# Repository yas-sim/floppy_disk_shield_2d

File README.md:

# Floppy Disk Shield for Arduino UNO

## Caveat and Disclaimer - Read before you build a fd-shield  

- I don't own any responsibility for the data loss or physical damage on your floppy disks or computer assets caused by the use of hardware and software included in this project.
- Hardware compatibility (especially, FDD and FD-Shield compatibility) is not guaranteed. Your FDD may now work with the FD-Shield.  
- The magnetic flux power on the old floppy disks are dropping and getting weak as time passes. Read-out data integrity with this system is not guaranteed.
- Recommended to use newer FDD. The old FDD may have problems on the magnetic head such as contamination, worn out or mechanical misalignment.

## Announcement  
23-Sep 2022 : Preview release - Feature to write back the floppy images to FD is supported. Use `duplicate.py` to write the `*.raw` floppy image data to a floopy disk. Arduino firmware update and closing `JP5` on the fd-capture shield are required to enable the feature.   
23-Sep 2022 : Preview release - イメージの書き戻しもできるようになりました。Arduinoファームウエアの更新と`JP5`ジャンパーのショートをすると書き込みができるようになります。   

## Description
This is a project to develop a system for preserving old 2D/2DD floppy disk data.  
The system can preserve entire floppy disk data regardless whether it's normal or not. That means the system can read and preserve copy protect information in the bit-stream file as it is.  
The recorded bit-stream file can be decoded and restore the contents anytime later.  
The system includes a bit-stream data to D77/D88 emulator disk image converter. You can read the floppy disk with this tool and generate the disk images.  
これは古い2D/2DDフロッピーディスクのデータを保存するためのシステムを作るプロジェクトです。  
このシステムを使うことで仕様にのっとった正しい信号も非正規の信号も全てそのまま保存することが可能です。つまり、このシステムではコピープロテクトのための情報まで含めてビットストリームデータとして保存することが可能です。  
記録されたビットストリームデータは後でデコード、解読を行うことで情報を取り出すことが可能です。  
このシステムにはビットストリームデータからエミュレータ互換のイメージファイル(D77/D88)を生成するためのコンバーターも含んでいます。実際のフロッピーを読み取り、ディスクイメージを生成することが可能です。  

The system consists of the hardware and software:  
システムはハードウエアとソフトウエアから構成されます:

**Hardware**  
|Item|Description|
|:----|:----|
|Arduino UNO|Arduino UNO. The firmware uses ATMega328 specific regiter. The other Arduino board may not work|
|Floppy disk shield for Arduino|Design data is included. Both schematics and PCB data are available (`./kicad/*`)<br>Rev.A design has bugs. Rev.B and beyond are basically comatible and has same function.<br>KiCAD用のPCBの設計データも提供されています(./kicad/*)<br>Rev.A and Rev.Fにはバグがあります。Rev.B以降は基本的に同じ機能です|
|Floppy disk drive|2D/2DD/2HD FDD. 3.5" or 5.25" FDD (+ power supply and ribbon cable). 300rpm drive is recommended but 360rpm 2HD drive will work as a 2DD drive. The FD-shield can detect the track density (2D or 2DD/2HD, 80 tracks or 160 tracks) and spindle spin speed (300rpm or 360rpm)|  

**Software**  

|Name|Description|
|:--------|:-----------|
|[`fdcapture.ino`](./docs/fdcapture_ino.md)|Arduino firmware (sketch) for the floppy shield<br> (`./fdcapture/fdcapture.ino`)|
|[`capture.py`](./docs/capture.md)|Floppy image capture tool (FD->image).<br>Transfers raw bitstream data from Arduino to a PC (foremerly, `transfer.py`)|
|[`duplicate.py`](./docs/duplicate.md)|Floppy image write back tool (image->FD).<br>Transfers raw bitstream data from a PC to Arduino. Close '`JP5`' jumper pad on the FD capture shield to enable the write feature.|
|[`bs2d77.py`](./docs/bs2d77.md)|Bit-stream data (.raw) to emulator disk image (D77/D88) converter.<br> The program generates modified D77 image data (D77mod). D77mod specification is [here](docs/D77mod_format.md). The D77mod uses some reserved bytes in the header but it is designed to keep backward compatibility with the standard D77 disk images. The D77mod image should work with emulators which supports regular D77/D88 disk images.|
|[`bs2hfe`](./docs/bs2hfe.md)|Bit-stream data (.raw) to .HFE floppy image format.<br>The .hfe disk image format is used for the [HxC FDD emulator device](https://hxc2001.com/download/floppy_drive_emulator/).|
|[`bs_inspect.py`](./docs/bs_inspect.md)|Data inspection/analyze tool for bit-stream data|
|[`d77_inspect.py`](./docs/d77_inspect.md)|Data inspection/analyze tool for D77/D88 disk image data|
|`floppylib.py`|A library which provides fundamental floppy disk functions.<br> This library is including data-separator, digital VFO, MFM decoder and IBM format parser|
|`d77dec.py`|Convert a D77/D88 disk image data to a JSON (plane text) file|
|`d77enc.py`|Generate a D77/D88 disk image data from a JSON file|
|`d77lib.py`|A libray which provides basic D77/D88 floppy disk image manipulation functions|
|[`kfx2bs.py`](./docs/kfx2bs.md)|[**KyroFlux**](https://www.kryoflux.com/) raw-bitstream data to fd-shield bit-stream data converter. You can capture FD image with KryoFlux and use it.|

### Updates  
|Date|Description|
|-|-|
|Sep 2022|Updated PCB design. Changed the 'Write Gate' jumper from jumper pad to jumper pin header for easy setting.|
|Sep 2022|Added support for the image write back feature (image->fd). Arduino firmware update and closing `JP5` on the fd-capture shield are required to enable the feature.|
|Sep 2022|Added RAW to HFE file converter (bs2hfe.py)|
|Aug 2022|Backported data-separator and VFO algorithm from [fdc_bitstream](https://github.com/yas-sim/fdc_bitstream) project. The latest VFO algorithm improved the accuracy of the data reading / decoding.|

## fdc_bitstream  
The [`fdc_bitstream`](https://github.com/yas-sim/fdc_bitstream) is my project that provides a bit-accurate C++ software FDC library. The fdc_bitstream project includes a disk image converter and image analyzer. Those software are written in C++, so they are faster than the converters in this project. Also, they are developed recently and have better algorithms for format conversion.  Please try `image_converter` in the `fdc_bitstream` project as well.  
[`fdc_bitstream`](https://github.com/yas-sim/fdc_bitstream)はビット精度で正確なソフトウエアFDCを開発するプロジェクトです。fdc_bitstreamプロジェクトにもイメージ変換ツールとイメージ解析ツールが含まれています。これらのツールはC++でかかれており、より高速です。またこちらのほうが開発が後なのでより良いアルゴリズムが使われており、イメージ変換の正確性も上がっています。fdc_bitstreamプロジェクトのimage_converterもお試しください。  

### System Diagram

## FD-Shield - How It Works

---------

## Introduction of Features in the Support Tools

* `bs_inspect.py`  
This tool provides featurs to analyze or check the bitstream data and its quality.  
	* Visualize track data including address mark and sector data occupancies.
	* Visualize data timing history.
	* Visualize data timing histogram.
	* Read all IDs in the tracks.
	* Read all sectors in the tracks.
	* MFM data dump.
	* ASCII data dump (display pritable/readable data).
	* Tweak parameters (VFO high/low gain value, sampling frequency, FDD spin speed) .

### Track visualizer  
You can check the address marks and sector body overlap status with this feature. The entire track data is shown in the window. The yellow vertical line indicates the position of the index hole (it appears when you capture the track data with --read_overlap option). This feature can show the decoded MFM data at the point of the mouse cursor.   

* Legend:  
	* Red ID               : ID CRC Error
	* Green virtical line  : ID AM / Index AM
	* Cyan virtical line   : DAM / DDAM
	* Cyan horizontal line : Sector data (normal)
	* Magenta horizontal line : Sector data (Data CRC error)
	* Red cross mark       : Record not found error
	* Yellow virtical line : Index hole  
<br>  

* Example of a normal track  

* Example of a protected track  

### Bitstream visualizer  
You can check how VFO follows the variation of pulse pitch with the bitstream visualizer.  
The VFO tries to keep the data pulse be the center of the bit cell as much as possible by tweaking the oscillation frequency (= the bit cell width).  

### Bitstream timing histogram viewer
* Good case 
* Bad case - Usually, this may be caused by the spindle speed fluctuation (that causes data pulse pitch variation in a track), or data written by multiple drives (written with drives with different spindle motor speeds).  

### Pulse (bit) pitch visualizer  
You can check the pulse pitch fluctuation throughout a track with the pulse pitch visualizer. The stabler pitch, the easier MFM decode or data read.  
- Stable pitch  

- Unstable pitch. Heavily fluctuated. It's so hard to follow by the VFO. May fail data retrieving.  

---------

## How to use (Image capture) - 使い方

1. Build Floppy shield for Arduino UNO - シールド製作  
- PCB design files can be found in the `./kicad` directory
2. Burn the floppy disk shield firmware (sketch) to Arduino UNO - Arduio UNOにファームウエアを書き込む  
Use `fdcapture.ino`
3. Assemble the system - システムを接続
- Attach a floppy shield to an Arduino UNO
- Connect a floppy shield and a floppy disk drive with a 36pin ribon cable
- Connect Arduino UNO to PC via USB cable
4. Read raw bit-stream data from a floppy disk - フロッピーからビットストリームデータを生成  
- Insert a 2D floppy disk to the floppy disk drive (FDD)
- Run following command on the Windows PC:
```sh
python capture.py -o image_name.raw --read_overlap 5 [--media_type 2D|2DD]
```
- `capture.py` will search COM port for Arduino UNO and use it.  
- `--read_overlap` option specifies how much data to read on the 2nd lap in percent.  
- `--media_type` option specifies the media type to read. `2D` or `2DD` are available.  
Note: The `fdcapture.ino` can identify the drive type (2D or 2DD) but not the media type.    
5. Convert raw bit-stream data into emulator image data (D77mod) -- ビットストリームからディスクイメージファイルを生成
```sh
python bs2d77.py -i image_name.raw --abort_id
```
- `image_name.d77` will be generated.  
**Note:** The `--abort_id` option enables abort reading track image when the same sector ID is detected. The FD-shield can read the top of the 2nd lap with `--read_overlap` option. This overlapped track data may contain the same sector data twice. This option will prevent from generating the same sector in a track.  

## Image write back (cloning)  
1. Setup the system as the same as image captureing.  
	- The same `fdcapture.ino` firmware works for both `capture.py' and 'duplicate.y' but updating to the latest firmware is required. Use Arduino IDE to update the firmware (Arduino program).    
	- Close `JP5` jumper pad on the fd-capture shield.  
2. Run '`duplicate.py`' to write back a '`*.raw`' floppy image to a floppy disk.  
```sh
python duplicate.py -i disk_image.raw
```

## How to make your own FD-shield PCB (FD-shield PCBの作り方)  
- PCB design data and the data for PCB manufacturing (Garber data and drill data) are included in this project. You can order your PCB at a PCB manufacturing service company. I used 'Fusion PCB' from Seeed Studio. (cost would be around $35 for 10 PCBs incl. delivery fee)    
- PCB設計データとPCB製造データ(ガーバー、ドリル)はこのプロジェクトに含まれています。PCB製造サービス会社に製造を依頼してPCBを手に入れることができます。私はSeeed StudioのFusion PCBを利用しました。(10枚で4K円くらい？ 送料込み)   

|File|Description|  
|---|---|  
|pcb_mfg_data/fdshield-dip-rev-h.zip|PCB manufacturing data. DIP version. Rev.H (Write Gate pin header)|  
|kicad/fdshield-dip/fdshield/fdshield.kicad_pro|KiCad v6 design file (DIP)|  
|kicad/fdshield-sop/fdshield/fdshield.kicad_pro|KiCad v6 design file (SOP)|  

## Accessory Tools  
1. FDD spindle motor speed calibration tool  
This tool measures the index hole to index hole time and show it on the screen. You can tweak a variable register on the FDD control board to adjust the spindle speed.  
**CAUTION**: There might be multiple variable registers on the FDD control board. If you are unsure which one is the right one, do not turn it, or your FDD will become unfunctional.  
- How to use:  
	1. Set up `fdcapture` shield - Connect Arduino UNO, fdcapture shield, and FDD.   
	2. Insert a floppy disk into the FDD.  
	3. Run `spindle_calibration_tool.py`

## Current Development Status
**Done:**
- Read floppy disk images (2D disk on 2D drive, 2DD disk on 2D deive, 2D disk on 2DD/2HD drive)
- Write floppy disk image to floppy disk (2D images are tested)  
- Drive type auto datection (2D or 2DD/2HD)
- Drive spindle revolution measurement 
- Generates D77mod disk images from the raw bitstream data (RAW->D77)
- RAW->HFE file converter
- Bit stream file quality inspection tool (bs_inspect.py)

## Test Environment

- Windows 10 1909 / Windows 11 21H2
- Arduino UNO
- Floppy disk shield for Arduino
- FDDs (table below)

|P/N|Mfg|FF|Description|
|:----|:----|:----:|:----|
|YD-580 1354|YE-Data|5.25"|2D, 300rpm, for Fujitsu FM-7|
|MD5201|Canon|5.25"|2D, 300rpm|
|FD-55B-01-U 19307110-01|TEAC|5.25"|2D, 300rpm|
|FD55-GFR 19307673-93|TEAC|5.25"|2DD/2HD, 360rpm, for DOS/V|
|YD625-1525|YE-Data|3.5"|2D, 300rpm, for Fujitsu FM-77|
|FD-235HG 19307773-04|TEAC|3.5"|2DD/2HD, 300/360rpm, Fixed to DS1|
|OSD E26J|Citizen|3.5"|2DD/2HD, 300/360rpm, for PX9821Xa?|
|JU-256A236P|Panasonic|3.5"|2DD/2HD, 300/360rpm, for DOS/V|
|FD1231T 134-506790-011-0|NEC|3.5"|2DD/2HD, 300/360rpm, for PC9821|
|DF354H068C|ALPS|3.5"|2DD/2HD, 300/360rpm, for DOS/V|

---------------

## Addendum

### FD-shield - 3D view

### FD-shield - Schematics  
Y1 (Xtal) = 4MHz X'tal.  
U6 must be '74HC**U**04' (unbuffered type). The standard '74HC04' doesn't work.  
The other logic ICs can be either one of '74LS' or '74HC'.  

[PDF](resources/fdshield-schematics.pdf)

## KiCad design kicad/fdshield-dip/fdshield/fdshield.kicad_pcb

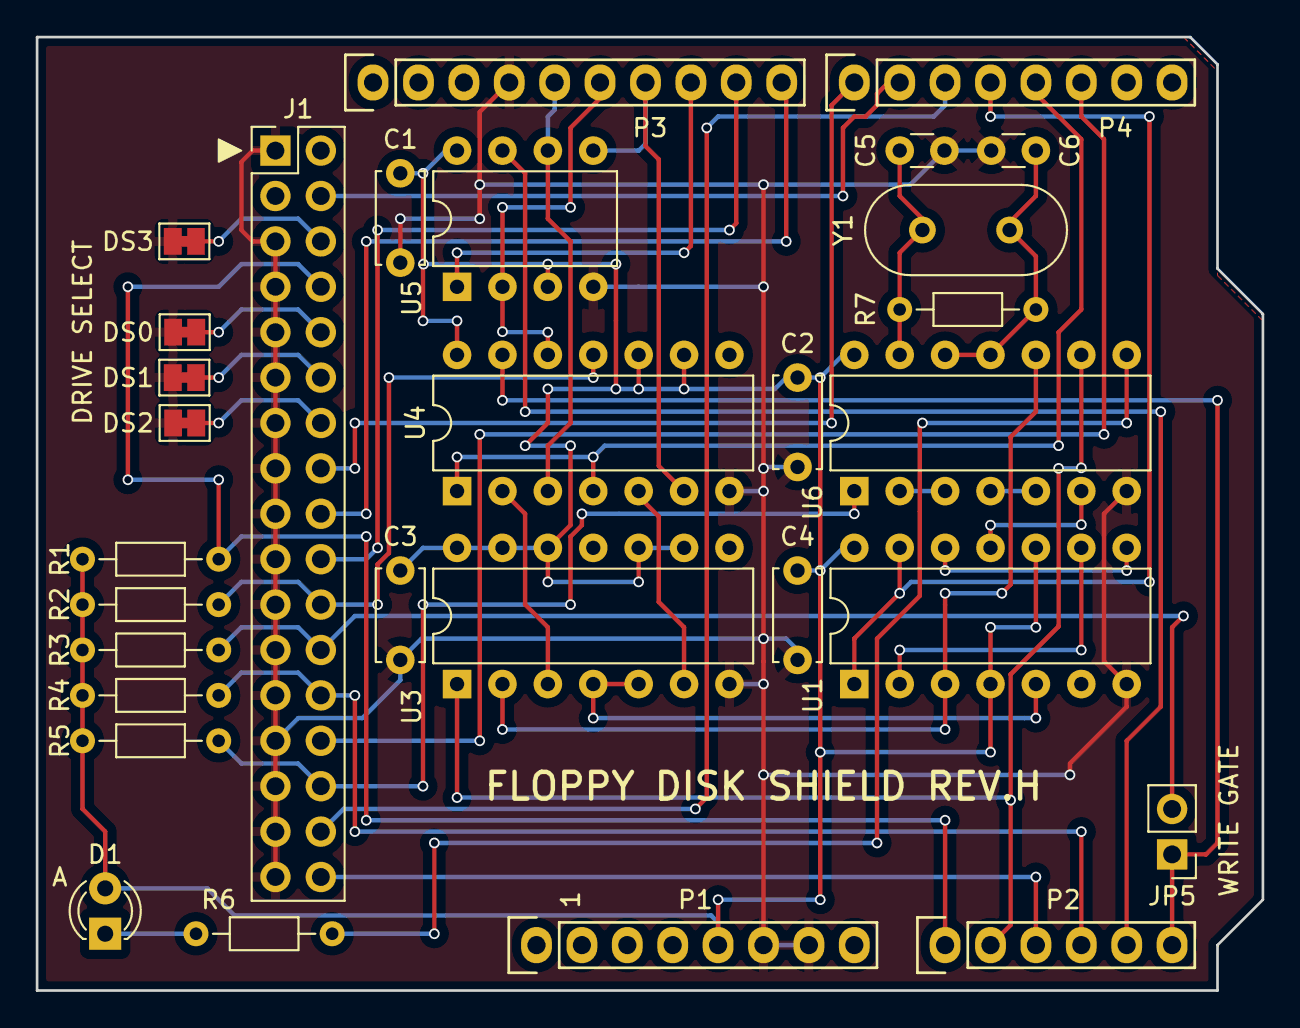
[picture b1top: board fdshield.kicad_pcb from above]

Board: 2 copper layers, 68.6 x 53.3 mm, 30 parts (0 on the bottom side), 40 nets.

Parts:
C1, C2, C3, C4: 0.1u; C_Disc_D5.0mm_W2.5mm_P5.00mm
C5, C6: 22p; C_Disc_D3.0mm_W1.6mm_P2.50mm
D1: LED; LED_D3.0mm
DS0, DS1, DS2, DS3: SolderJumper_2_Bridged; SolderJumper-2_P1.3mm_Bridged_Pad1.0x1.5mm
J1: Conn_02x17_Odd_Even; PinHeader_2x17_P2.54mm_Vertical
JP5: WRITE GATE; PinHeader_1x02_P2.54mm_Vertical
P1: Power; Socket_Strip_Arduino_1x08
P2: Analog; Socket_Strip_Arduino_1x06
P3: Digital; Socket_Strip_Arduino_1x10
P4: Digital; Socket_Strip_Arduino_1x08
R1, R2, R3, R4, R5: 150; R_Axial_DIN0204_L3.6mm_D1.6mm_P7.62mm_Horizontal
R6: 470; R_Axial_DIN0204_L3.6mm_D1.6mm_P7.62mm_Horizontal
R7: 1M; R_Axial_DIN0204_L3.6mm_D1.6mm_P7.62mm_Horizontal
U1: 74LS74; DIP-14_W7.62mm
U3: 74LS08; DIP-14_W7.62mm
U4: 74LS125; DIP-14_W7.62mm
U5: 23LCxxx; DIP-8_W7.62mm
U6: 74HCU04; DIP-14_W7.62mm
Y1: Crystal; Crystal_HC49-U_Vertical

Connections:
+5V: C1.1, C2.1, C3.1, C4.1, D1.2 (A), P1.5, R1.1, R2.1, R3.1, R4.1, R5.1, U1.4 (~S), U1.10 (~S), U1.14 (VCC), U3.9, U3.10, U3.12, U3.13, U3.14 (VCC), U4.9, U4.10, U4.14 (VCC), U5.3 (~WP), U5.8 (VCC), U6.14 (VCC)
/2: J1.28, P4.6
/3(**): P4.5, U4.1, U4.4
/4: P4.4, U1.1 (~R), U1.13 (~R)
/5(**): J1.32, P4.3
/6(**): J1.4, P4.2
/7: J1.16, P4.1
/8: J1.18, P3.10
/9(**): J1.20, P3.9
/10(**/SS): P3.8, U5.1 (~CS)
/11(**/MOSI): P3.7, U4.6, U5.5 (MOSI)
/12(MISO): P3.6, U4.12, U5.2 (MISO)
/13(SCK): P3.5, U4.3, U5.6 (SCK)
/A0: J1.8, P2.1, R1.2
/A1: P2.2, U3.1, U6.9
/A2: J1.34, P2.3
/A3: J1.26, P2.4, R4.2
/A4: P2.5, U5.7 (~HOLD)
/A5: JP5.1 (A), P2.6, U4.13
/CAP_CLK: U1.3 (C), U3.2, U6.10
/DS0: DS0.1 (A), J1.10
/DS1: DS1.1 (A), J1.12
/DS2: DS2.1 (A), J1.14
/DS3: DS3.1 (A), J1.6
/RD: J1.30, R5.2, U6.1
/WD: J1.22, R2.2, U4.11
/WG: J1.24, JP5.2 (B), R3.2
GND: C1.2, C2.2, C3.2, C4.2, C5.2, C6.2, DS0.2 (B), DS1.2 (B), DS2.2 (B), DS3.2 (B), J1.1, J1.5, J1.7, J1.9, J1.11, J1.13, J1.15, J1.17, J1.19, J1.21, J1.23, J1.25, J1.27, J1.29, J1.31, J1.33, P1.6, P1.7, P3.4, U1.7 (GND), U3.7 (GND), U4.7 (GND), U5.4 (GND), U6.7 (GND)
unnamed: C5.1, R7.2, U6.13, Y1.1
unnamed: C6.1, R7.1, U6.11, U6.12, Y1.2
unnamed: D1.1 (K), R6.1
unnamed: R6.2, U6.8
unnamed: U1.2 (D), U1.9 (Q)
unnamed: U1.5 (Q), U3.4, U3.5
unnamed: U1.11 (C), U6.6
unnamed: U1.8 (~Q), U1.12 (D)
unnamed: U3.3, U4.2
unnamed: U3.6, U4.5
unnamed: U6.2, U6.3
unnamed: U6.4, U6.5

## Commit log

2020-07-18 add floppy_shield.py and change image format +'~'
2020-07-18 moved MFM decode to data separator
2020-07-18 add 2dd/2hd drive support
2020-07-18 add kicad data
2020-07-18 added frontend
2020-07-18 added test code
2020-07-27 Added KryoFlux converter
2020-07-28 temporary commit
2020-07-29 daily commit
2020-07-31 add spin speed detection
2020-08-01 add transfer.py
2020-08-02 added fdshield DIP version design files
2020-08-08 added options for abort condition
2020-08-08 PCB FAB-F. Add write back feature
2020-08-08 added pictures
2020-08-08 rename to fdshield-sop
2020-08-08 modified README.md
2020-08-08 updated documents
2020-08-09 removed old PCB design archives
2020-08-09 organized PCB design data
2020-08-09 updated redame.md
2020-08-10 added command interface to arduino firmware
2020-08-10 added seek command to arduino FW
2020-08-10 added schematics
2020-08-10 added some Japanese description
2020-08-10 fixed minor document errors
2020-08-11 separated data bit extractor from the data separator
2020-08-14 document update
2020-08-15 added principal of operation diagram
2020-08-15 updated document
2020-08-18 added license file
2020-08-21 Same ID abort feature improved
    Same ID abort feature will be enabled only after 200ms passed from the
    top of the track.
    Added a feature to track the time of the reading pointer in the
    bitstream in the data_separator.
2020-08-22 Change step pulse generation
    Previously, step pulse was 1/2 step rate + 1/2 steprate duty.
    After improvement, the step pulse is 1us negative pulse.
    FM-77AV (MB8876A FDC) generates step pulse of 8ns negative pulse.
2020-08-22 Add read_overlap limitation logic
    Calculate the max capacity of the SPI SRAM and limit the read overlap
    parameter when it exceeds the max SPI SRAM capacity.
2020-08-22 Improved FDD type detect logic
2020-08-22 Daily commit
    - multiple address mark support (MB8877)
    - fixed bug in drive type detection in fdcapture.ino
2020-08-23 convert floppylib.py to a module
2020-08-23 add support tool descritions
2020-08-23 add pictures
2020-08-28 added dumpMFM16
2020-08-29 Mark MC bytes in yellow in timing history graph
2022-08-11 new ds working
2022-08-11 modified functions in bs_inspect.py for new DS
    Modified the code to make it compatible with the new data separator.
2022-08-16 Change index hole detection algorithm
2022-08-24 Fixed bug in bs2.d77 (output file name)
2022-08-24 Fixed a bug in fdcapture.ino
    Wrong RAW encode happened when the pulse pitch is too long and
    a variable 'count' get overflowed.
2022-08-26 Added support for new RAW spec (timing extension)
2022-08-26 Added new RAW decode capability in floppylib
2022-08-26 fdcapture dumps only 'captured' data.
    previously, fdcapture dumps all data stored in the SPI SRAM regardless
    how much data is captured from the FDD.
    Now it dumps only the real, captured data portion only.
2022-08-26 Add VFO class for data separator
2022-08-26 Add VFO support for bs_inspector.py
2022-08-26 Ignore MC check on cloch phase
2022-08-26 Ignore MC compare on clock cycle
2022-08-26 Ignore MC comp on CLK in bs_inspect.py
2022-08-27 Add 2HD parameter support
    - fdcapture.ino
    - Reports sampling rate (4MHz)
    - transfer.py
    - Accept 2HD as media type
    - Determine bit rate and track range from the media type.
2022-08-27 Fixed 2DD/2D step issue
2022-08-31 Added vfo_pid3. Made vfo_pid3 the default vfo.
2022-08-31 Change default gain settings
2022-09-01 Update Readme. Add pulse pitch visualizer
2022-09-02 Fixed minor bug in pulse pitch viewer
2022-09-02 update images
2022-09-07 Update document
2022-09-08 Added spindle_calibration_tool.py
2022-09-08 Split fdcapture.ino into multiple files
2022-09-16 Added bs2hfe.py.
2022-09-17 Fixed bug in bs2hfe.py (track offset table size)
2022-09-22 Initial implementation of duplicate.py
2022-09-23 working-1
2022-09-23 Initial release with write back feature
2022-09-23 removed a document
2022-09-23 update system diagram
2022-09-27 Added WP status check in duplicate.py
2022-09-28 JP5(WG) changed from solder jumper to pin header
2022-09-29 Added bit pulse timing normalizer function
2022-09-29 removed unnecessary message
2022-09-29 minor change
2022-09-29 Added SPI SRAM overflow check
2022-09-29 2HD normalization (comment out)
2022-09-30 PCB data update (WG) (rev_h)
2022-10-01 Optimized write sequence
2022-10-02 Added IDAM time calculation in bs_inspect
2022-10-10 Arduino timer calib. + track visualizer.
    Added 'track visualizer' in bs_inspector.py
    Added support for Arduino timer1 clock calibration.
    - fdcapture.ino
    - Added 'M' command to measure the Arduino timer1 count speed
    - Added 'S' command to set the calibrated timer clock value
    - Changed track read and track write to use timer1 for timing
2022-10-10 added images
2022-10-10 updated picture
2022-10-10 Improved track visualizer in bs_inspect.py
    - ID-CRC error support
    - Data CRC error support
    - RNF error support
2022-10-10 Added ascii dump support in track visualizer in bs_inspect.py
2022-11-03 Added kfx_2dd_to_2d.py
2022-11-03 Add temporary code to support non-genuine Arduino Uno compatible boards.
2023-11-22 FRAM CY15B104Q support
2023-11-23 F-RAM support - 2HD read succeeded
